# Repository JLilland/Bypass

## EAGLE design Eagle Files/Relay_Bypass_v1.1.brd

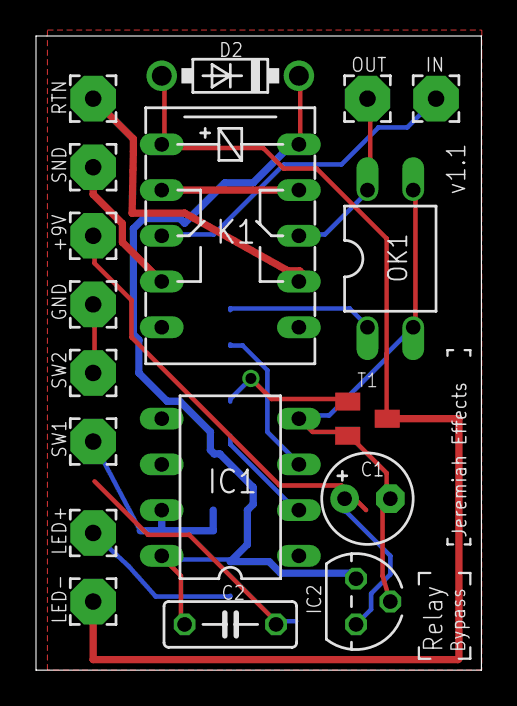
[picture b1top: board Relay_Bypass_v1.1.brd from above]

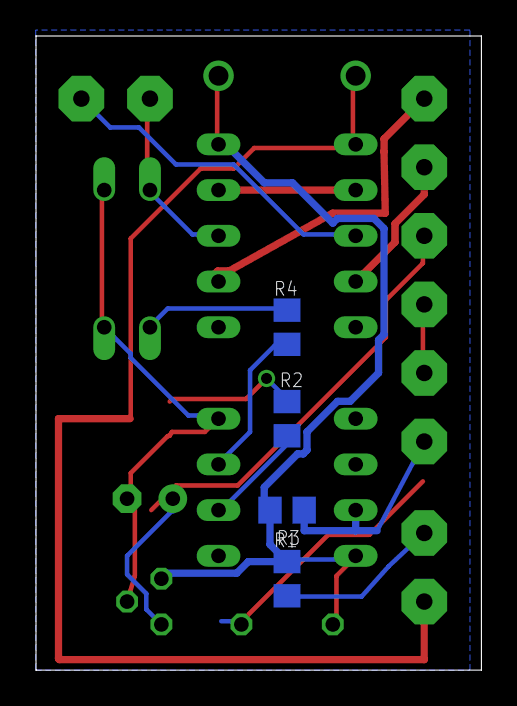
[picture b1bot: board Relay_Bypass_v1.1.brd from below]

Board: 2 copper layers, 24.7 x 35.2 mm, 22 parts (4 on the bottom side), 15 nets.

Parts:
+9V: 2,54/0,9
C1: 100uF; E2,5-5
C2: 100n; C050-025X075
D2: 1N5817-B; DO41-7.6
GND: 2,54/0,9
IC1: TINY15LP; DIL08
IC2: 78L05Z; TO92
IN: 2,54/0,9
K1: G6H2-100
LED+: 2,54/0,9
LED-: 2,54/0,9
OK1: LTV816; DIL04
OUT: 2,54/0,9
R1, R2: 10k; R0805
R3: clr; R0805
R4: 1k; R0805
RTN: 2,54/0,9
SND: 2,54/0,9
SW1, SW2: 2,54/0,9
T1: BC849; SOT23

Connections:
GND: C1.-, C2.2, GND.1, IC1.4, IC2.2, OK1.2, OK1.3, SW2.1, T1.2
unnamed: IC1.7, R1.1, SW1.1
unnamed: +9V.1, C1.+, IC2.3
unnamed: OK1.1, R4.1
unnamed: K1.P2, OK1.4, OUT.1
unnamed: IN.1, K1.P1
unnamed: K1.O1, K1.O2
unnamed: K1.S2, RTN.1
unnamed: IC1.2, R2.2
unnamed: IC1.3, R4.2
unnamed: R2.1, T1.1
unnamed: D2.A, K1.1, LED-.1, T1.3
unnamed: K1.S1, SND.1
unnamed: LED+.1, R3.2
VCC: C2.1, D2.C, IC1.8, IC2.1, K1.10, R1.2, R3.1

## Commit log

2017-04-19 Added Arduino file
    ...
2017-04-19 Commit Test
    tested making commit from github.com
2017-04-19 Added Eagle Files
    ...
2017-04-19 Code Edits
    test
2017-06-24 Cleanup
    Optimized and cleaned up code. Still room for debounce time
    optimization.
2017-06-24 File name change
2018-07-04 Created 3PDT Board
    Created 3PDT Project and ordered PCB, and rearranged files.
